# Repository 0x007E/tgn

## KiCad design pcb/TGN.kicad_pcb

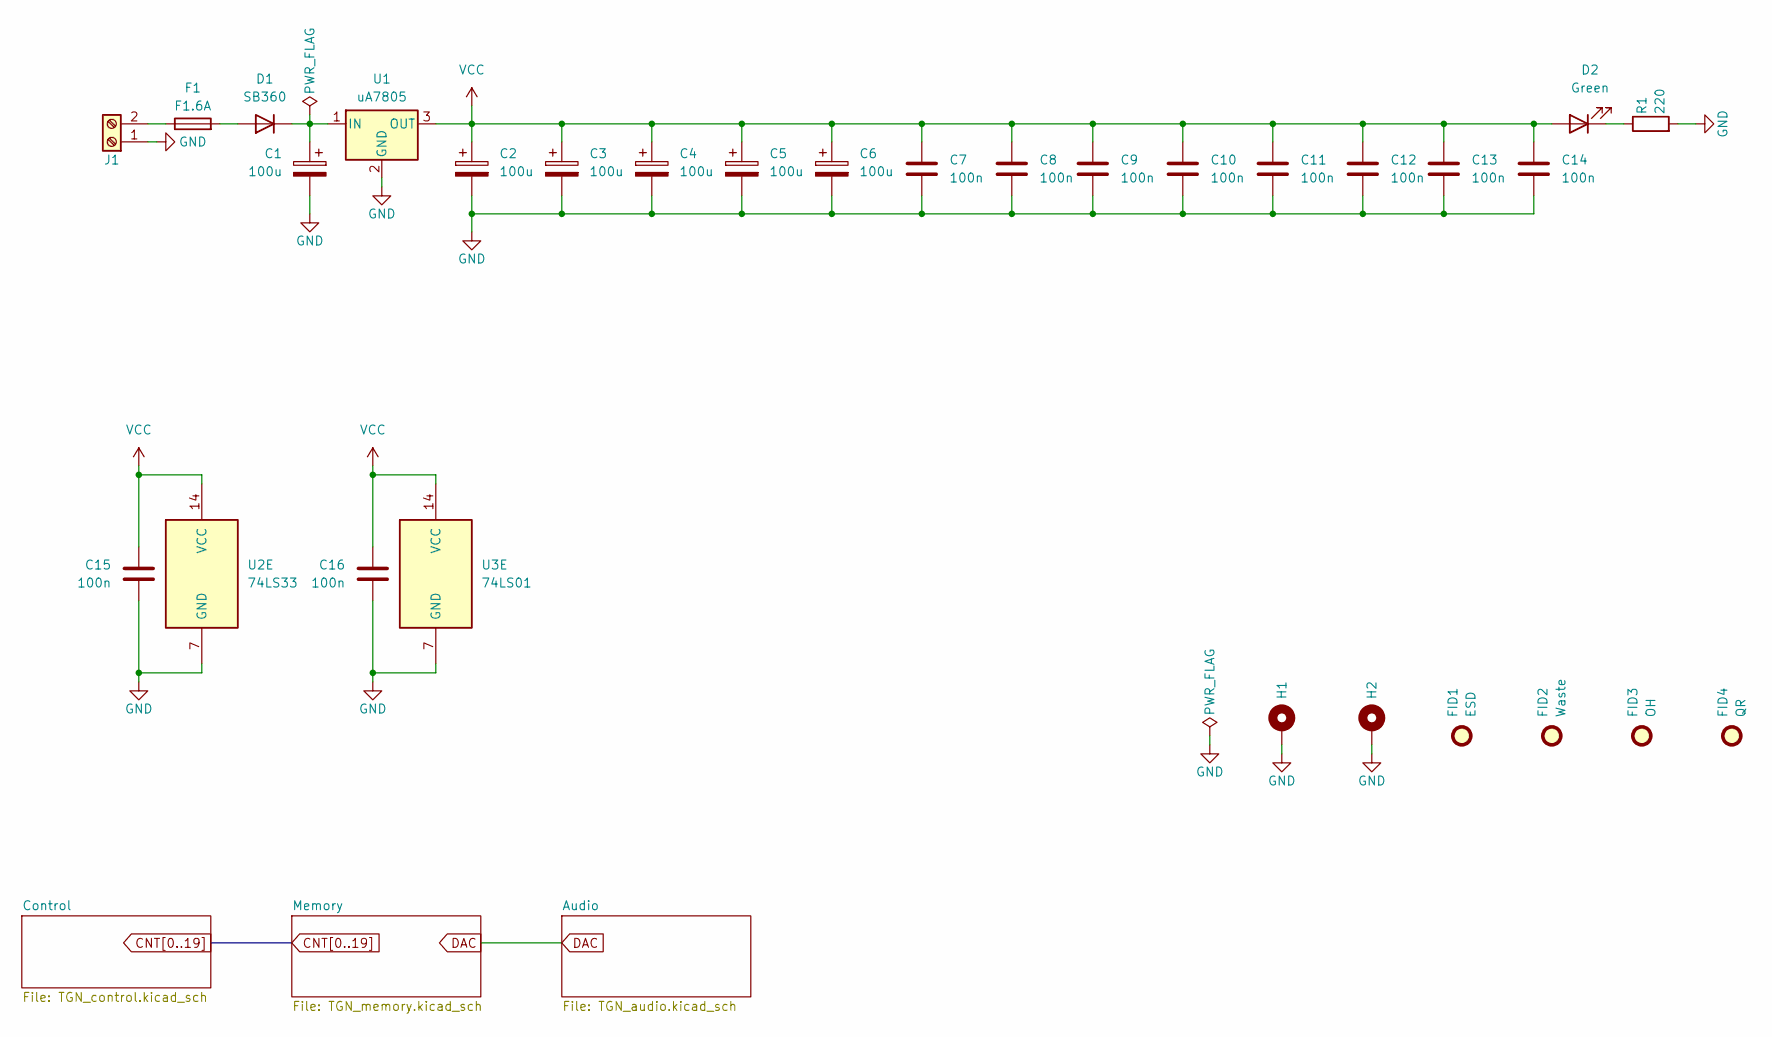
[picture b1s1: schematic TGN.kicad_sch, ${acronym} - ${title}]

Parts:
C1, C2, C3, C4, C5, C6: 100u; CP_Radial_D8.0mm_P3.50mm
C7, C8, C9, C10, C11, C12, C13, C14, C15, C16: 100n; C_Disc_D5.0mm_W2.5mm_P2.50mm
D1: SB360; D_DO-201_P15.24mm_Horizontal
D2: Green; LED_D5.0mm
F1: F1.6A; Fuse_20mm_HTL
FID1: ESD; ESD-Logo_6.6x6mm_SilkScreen
FID2: Waste; WEEE-Logo_4.2x6mm_SilkScreen
FID3: OH; OSHW-Logo_5.7x6mm_SilkScreen
FID4: QR; QR_0x007e_small
H1, H2: MountingHole_Pad; MountingHole_3.2mm_M3_Pad
J1: Screw_Terminal_01x02; TerminalBlock_Phoenix_MKDS-1,5-2-5.08_1x02_P5.08mm_Horizont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
R1: 220; R_Axial_DIN0207_L6.3mm_D2.5mm_P10.16mm_Horizontal
U1: uA7805; TO-220-3_Vertical
U2: 74LS33; DIP-14_W7.62mm_Socket_LongPads
U3: 74LS01; DIP-14_W7.62mm_Socket_LongPads

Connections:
GND: C1.2, C2.2, C3.2, C4.2, C5.2, C6.2, C7.2, C8.2, C9.2, C10.2, C11.2, C12.2, C13.2, C14.2, C15.2, C16.2, H1.1, H2.1, J1.1, R1.2, U1.2 (GND), U2.7 (GND), U3.7 (GND); also elsewhere on the board
unnamed: D1.2 (A), F1.2
unnamed: C1.1, D1.1 (K), U1.1 (IN)
unnamed: D2.1 (K), R1.1
unnamed: F1.1, J1.2
VCC: C2.1, C3.1, C4.1, C5.1, C6.1, C7.1, C8.1, C9.1, C10.1, C11.1, C12.1, C13.1, C14.1, C15.1, C16.1, D2.2 (A), U1.3 (OUT), U2.14 (VCC), U3.14 (VCC); also elsewhere on the board

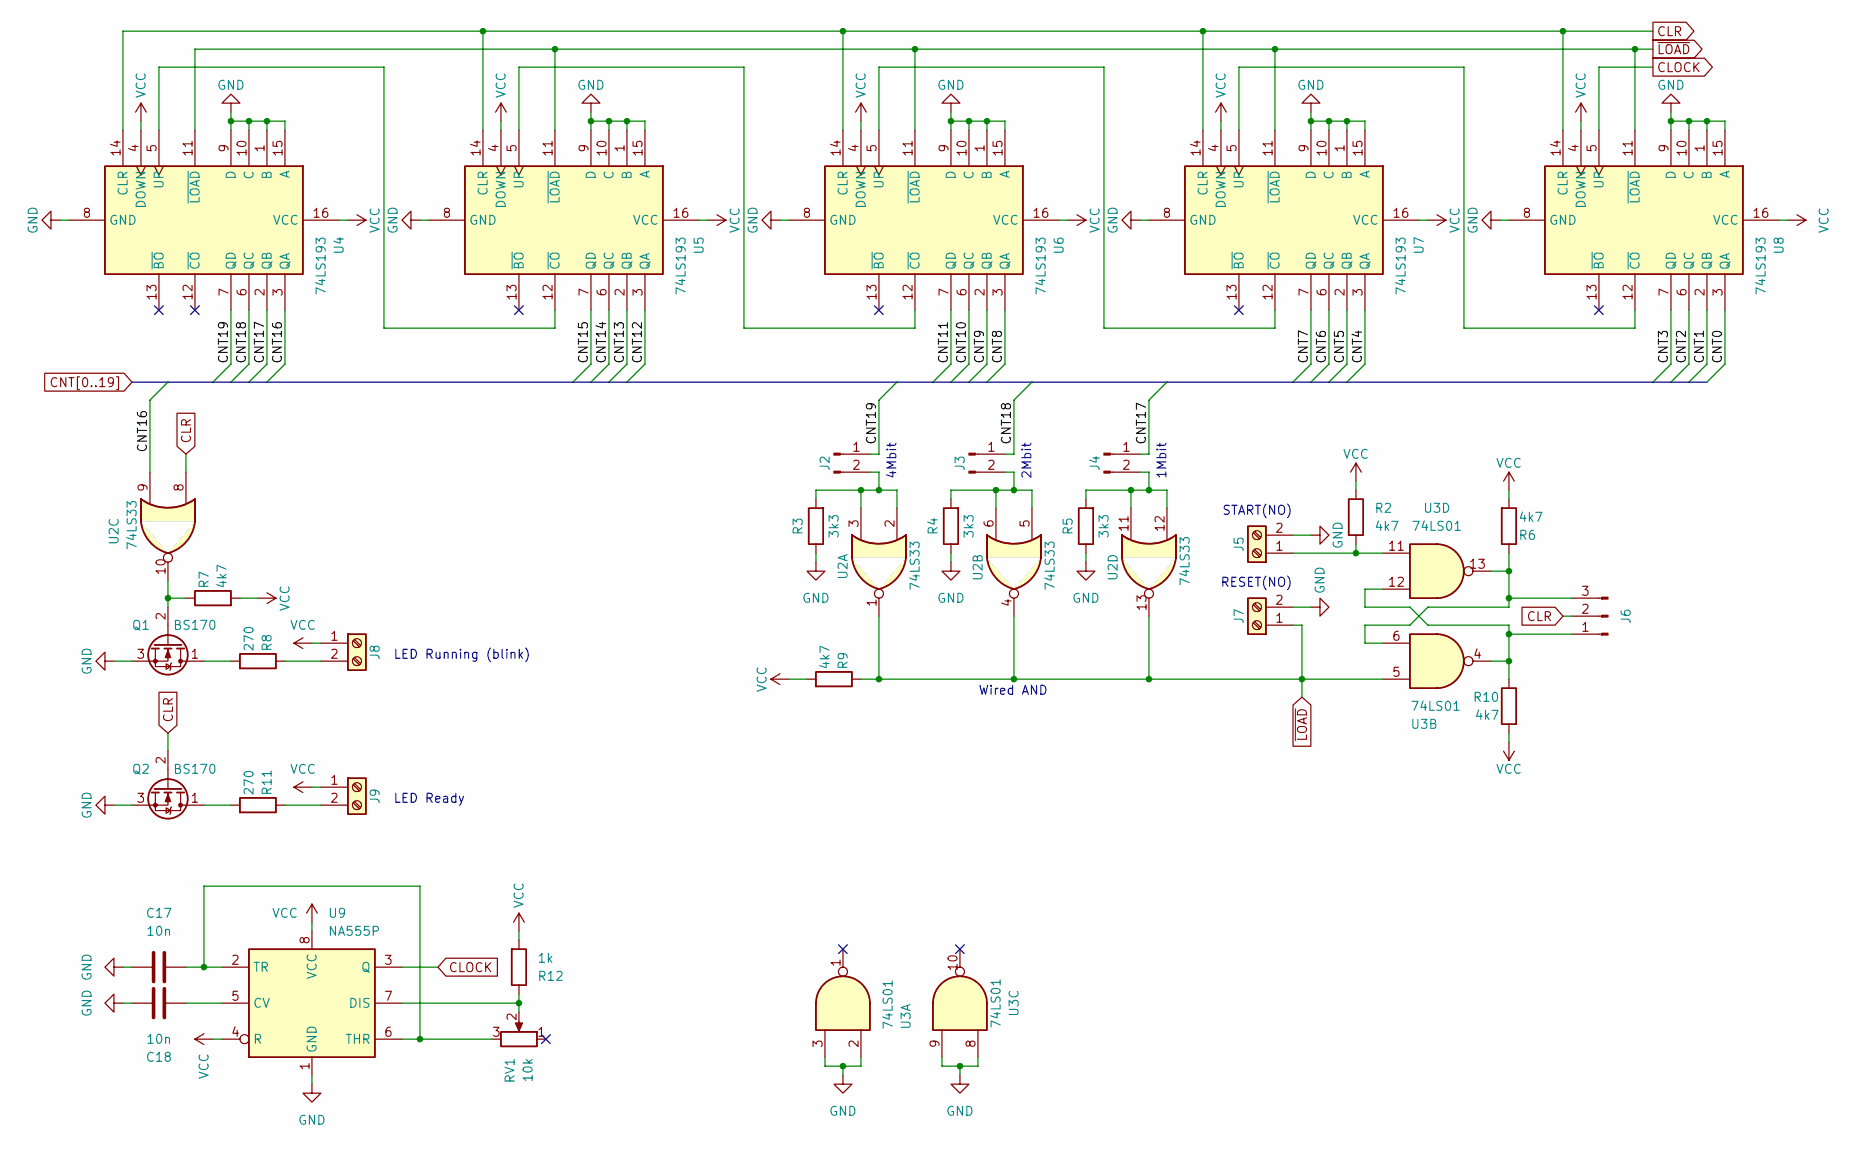
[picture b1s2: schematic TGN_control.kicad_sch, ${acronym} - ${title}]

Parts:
C17, C18: 10n; C_Disc_D5.0mm_W2.5mm_P2.50mm
J2, J3, J4: Conn_01x02_Pin; PinHeader_1x02_P2.54mm_Vertical
J5, J7, J8, J9: Screw_Terminal_01x02; TerminalBlock_Phoenix_MKDS-1,5-2-5.08_1x02_P5.08mm_Horizont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
J6: Conn_01x03_Pin; PinHeader_1x03_P2.54mm_Vertical
Q1, Q2: BS170; TO-92_Wide
R2, R6, R7, R9, R10: 4k7; R_Axial_DIN0207_L6.3mm_D2.5mm_P10.16mm_Horizontal
R3, R4, R5: 3k3; R_Axial_DIN0207_L6.3mm_D2.5mm_P10.16mm_Horizontal
R8, R11: 270; R_Axial_DIN0207_L6.3mm_D2.5mm_P10.16mm_Horizontal
R12: 1k; R_Axial_DIN0207_L6.3mm_D2.5mm_P10.16mm_Horizontal
RV1: 10k; Potentiometer_Bourns_3296W_Vertical
U2: 74LS33; DIP-14_W7.62mm_Socket_LongPads
U3: 74LS01; DIP-14_W7.62mm_Socket_LongPads
U4, U5, U6, U7, U8: 74LS193; DIP-16_W7.62mm_Socket_LongPads
U9: NA555P; DIP-8_W7.62mm_Socket_LongPads

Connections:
CLOCK: U8.5 (UP), U9.3 (Q)
CLR: J6.2, Q2.2 (G), U2.8, U4.14 (CLR), U5.14 (CLR), U6.14 (CLR), U7.14 (CLR), U8.14 (CLR)
CNT0: U8.3 (QA); also elsewhere on the board
CNT1: U8.2 (QB); also elsewhere on the board
CNT2: U8.6 (QC); also elsewhere on the board
CNT3: U8.7 (QD); also elsewhere on the board
CNT4: U7.3 (QA); also elsewhere on the board
CNT5: U7.2 (QB); also elsewhere on the board
CNT6: U7.6 (QC); also elsewhere on the board
CNT7: U7.7 (QD); also elsewhere on the board
CNT8: U6.3 (QA); also elsewhere on the board
CNT9: U6.2 (QB); also elsewhere on the board
CNT10: U6.6 (QC); also elsewhere on the board
CNT11: U6.7 (QD); also elsewhere on the board
CNT12: U5.3 (QA); also elsewhere on the board
CNT13: U5.2 (QB); also elsewhere on the board
CNT14: U5.6 (QC); also elsewhere on the board
CNT15: U5.7 (QD); also elsewhere on the board
CNT16: U2.9, U4.3 (QA); also elsewhere on the board
CNT17: J4.1, U4.2 (QB); also elsewhere on the board
CNT18: J3.1, U4.6 (QC); also elsewhere on the board
CNT19: J2.1, U4.7 (QD)
GND: C17.1, C18.1, J5.2, J7.2, Q1.3 (S), Q2.3 (S), R3.1, R4.1, R5.1, U3.2, U3.3, U3.8, U3.9, U4.1 (B), U4.8 (GND), U4.9 (D), U4.10 (C), U4.15 (A), U5.1 (B), U5.8 (GND), U5.9 (D), U5.10 (C), U5.15 (A), U6.1 (B), U6.8 (GND), U6.9 (D), U6.10 (C), U6.15 (A), U7.1 (B), U7.8 (GND), U7.9 (D), U7.10 (C), U7.15 (A), U8.1 (B), U8.8 (GND), U8.9 (D), U8.10 (C), U8.15 (A), U9.1 (GND); also elsewhere on the board
unnamed: J2.2, R3.2, U2.2, U2.3
unnamed: J3.2, R4.2, U2.5, U2.6
unnamed: J4.2, R5.2, U2.11, U2.12
unnamed: J5.1, R2.2, U3.11
unnamed: J6.1, R10.1, U3.4, U3.12
unnamed: J6.3, R6.1, U3.6, U3.13
unnamed: J8.2, R8.1
unnamed: J9.2, R11.1
unnamed: Q1.1 (D), R8.2
unnamed: Q1.2 (G), R7.1, U2.10
unnamed: Q2.1 (D), R11.2
unnamed: U4.5 (UP), U5.12 (~CO)
unnamed: U5.5 (UP), U6.12 (~CO)
unnamed: U6.5 (UP), U7.12 (~CO)
unnamed: U7.5 (UP), U8.12 (~CO)
unnamed: C18.2, U9.5 (CV)
unnamed: R12.1, RV1.2, U9.7 (DIS)
unnamed: C17.2, RV1.3, U9.2 (TR), U9.6 (THR)
VCC: J8.1, J9.1, R2.1, R6.2, R7.2, R9.2, R10.2, R12.2, U4.4 (DOWN), U4.16 (VCC), U5.4 (DOWN), U5.16 (VCC), U6.4 (DOWN), U6.16 (VCC), U7.4 (DOWN), U7.16 (VCC), U8.4 (DOWN), U8.16 (VCC), U9.4 (R), U9.8 (VCC); also elsewhere on the board
~LOAD: J7.1, R9.1, U2.1, U2.4, U2.13, U3.5, U4.11 (~LOAD), U5.11 (~LOAD), U6.11 (~LOAD), U7.11 (~LOAD), U8.11 (~LOAD)

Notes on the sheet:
Wired AND
2Mbit
4Mbit
LED Ready
1Mbit
LED Running (blink)
RESET(NO)
START(NO)

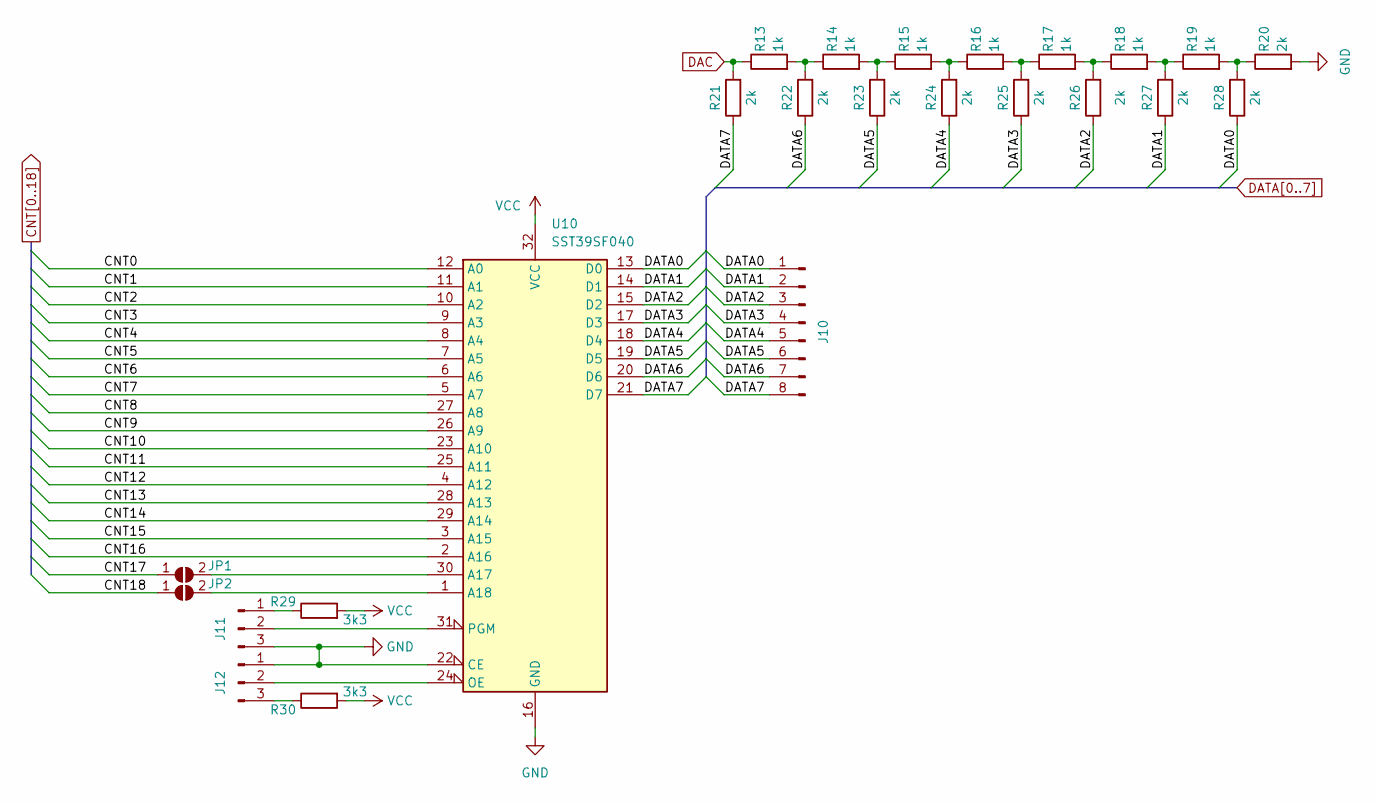
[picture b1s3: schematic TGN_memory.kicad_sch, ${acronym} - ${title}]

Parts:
J10: Conn_01x08_Pin; PinSocket_1x08_P2.54mm_Vertical
J11, J12: Conn_01x03_Pin; PinHeader_1x03_P2.54mm_Vertical
JP1, JP2: SolderJumper_2_Open; SolderJumper-2_P1.3mm_Open_RoundedPad1.0x1.5mm
R13, R14, R15, R16, R17, R18, R19: 1k; R_Axial_DIN0207_L6.3mm_D2.5mm_P10.16mm_Horizontal
R20, R21, R22, R23, R24, R25, R26, R27, R28: 2k; R_Axial_DIN0207_L6.3mm_D2.5mm_P10.16mm_Horizontal
R29, R30: 3k3; R_Axial_DIN0207_L6.3mm_D2.5mm_P10.16mm_Horizontal
U10: SST39SF040; DIP-32_W15.24mm_LongPads

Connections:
CNT0: U10.12 (A0); also elsewhere on the board
CNT1: U10.11 (A1); also elsewhere on the board
CNT2: U10.10 (A2); also elsewhere on the board
CNT3: U10.9 (A3); also elsewhere on the board
CNT4: U10.8 (A4); also elsewhere on the board
CNT5: U10.7 (A5); also elsewhere on the board
CNT6: U10.6 (A6); also elsewhere on the board
CNT7: U10.5 (A7); also elsewhere on the board
CNT8: U10.27 (A8); also elsewhere on the board
CNT9: U10.26 (A9); also elsewhere on the board
CNT10: U10.23 (A10); also elsewhere on the board
CNT11: U10.25 (A11); also elsewhere on the board
CNT12: U10.4 (A12); also elsewhere on the board
CNT13: U10.28 (A13); also elsewhere on the board
CNT14: U10.29 (A14); also elsewhere on the board
CNT15: U10.3 (A15); also elsewhere on the board
CNT16: U10.2 (A16); also elsewhere on the board
CNT17: JP1.1 (A); also elsewhere on the board
CNT18: JP2.1 (A); also elsewhere on the board
DAC: R13.1, R21.2; also elsewhere on the board
DATA0: J10.1, R28.1, U10.13 (D0)
DATA1: J10.2, R27.1, U10.14 (D1)
DATA2: J10.3, R26.1, U10.15 (D2)
DATA3: J10.4, R25.1, U10.17 (D3)
DATA4: J10.5, R24.1, U10.18 (D4)
DATA5: J10.6, R23.1, U10.19 (D5)
DATA6: J10.7, R22.1, U10.20 (D6)
DATA7: J10.8, R21.1, U10.21 (D7)
GND: J11.3, J12.1, R20.2, U10.16 (GND), U10.22 (CE); also elsewhere on the board
unnamed: J11.1, R29.1
unnamed: J11.2, U10.31 (PGM)
unnamed: J12.2, U10.24 (OE)
unnamed: J12.3, R30.1
unnamed: JP1.2 (B), U10.30 (A17)
unnamed: JP2.2 (B), U10.1 (A18)
unnamed: R13.2, R14.1, R22.2
unnamed: R14.2, R15.1, R23.2
unnamed: R15.2, R16.1, R24.2
unnamed: R16.2, R17.1, R25.2
unnamed: R17.2, R18.1, R26.2
unnamed: R18.2, R19.1, R27.2
unnamed: R19.2, R20.1, R28.2
VCC: R29.2, R30.2, U10.32 (VCC); also elsewhere on the board

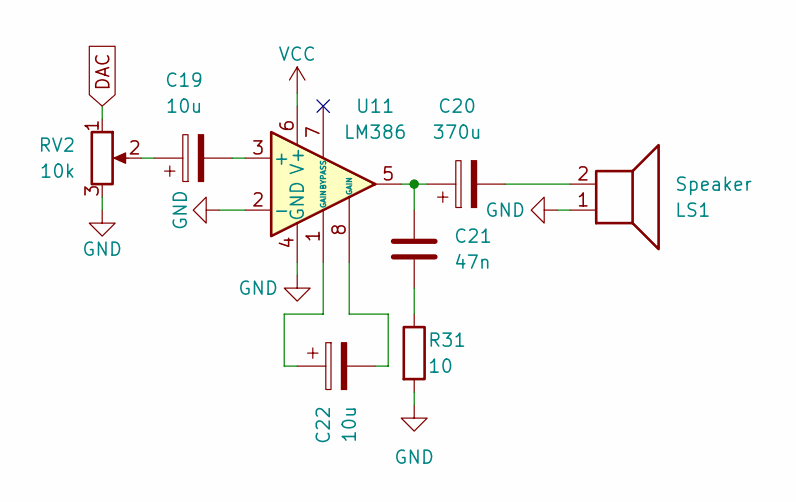
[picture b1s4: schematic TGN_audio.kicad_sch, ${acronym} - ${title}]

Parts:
C19, C22: 10u; CP_Radial_D8.0mm_P3.50mm
C20: 370u; CP_Radial_D8.0mm_P3.50mm
C21: 47n; C_Disc_D5.0mm_W2.5mm_P2.50mm
LS1: Speaker; TerminalBlock_Phoenix_MKDS-1,5-2-5.08_1x02_P5.08mm_Horizont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
R31: 10; R_Axial_DIN0207_L6.3mm_D2.5mm_P10.16mm_Horizontal
RV2: 10k; Potentiometer_Piher_PT-10-V10_Vertical
U11: LM386; DIP-8_W7.62mm_Socket_LongPads

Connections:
DAC: RV2.1; also elsewhere on the board
GND: LS1.1, R31.2, RV2.3, U11.2 (-), U11.4 (GND); also elsewhere on the board
unnamed: C19.1, RV2.2
unnamed: C20.1, C21.1, U11.5
unnamed: C20.2, LS1.2
unnamed: C21.2, R31.1
unnamed: C22.1, U11.1 (GAIN)
unnamed: C22.2, U11.8 (GAIN)
unnamed: C19.2, U11.3 (+)
VCC: U11.6 (V+); also elsewhere on the board

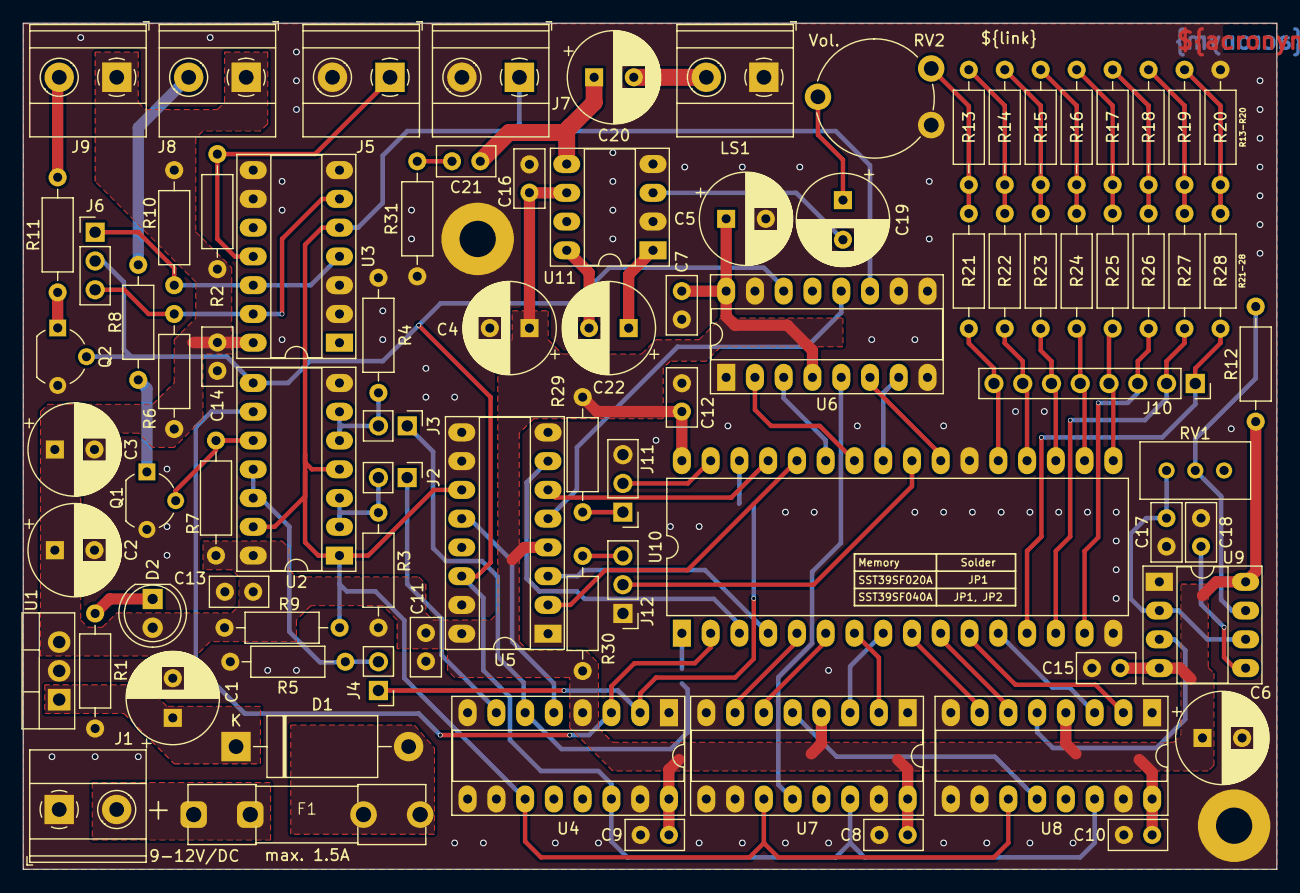
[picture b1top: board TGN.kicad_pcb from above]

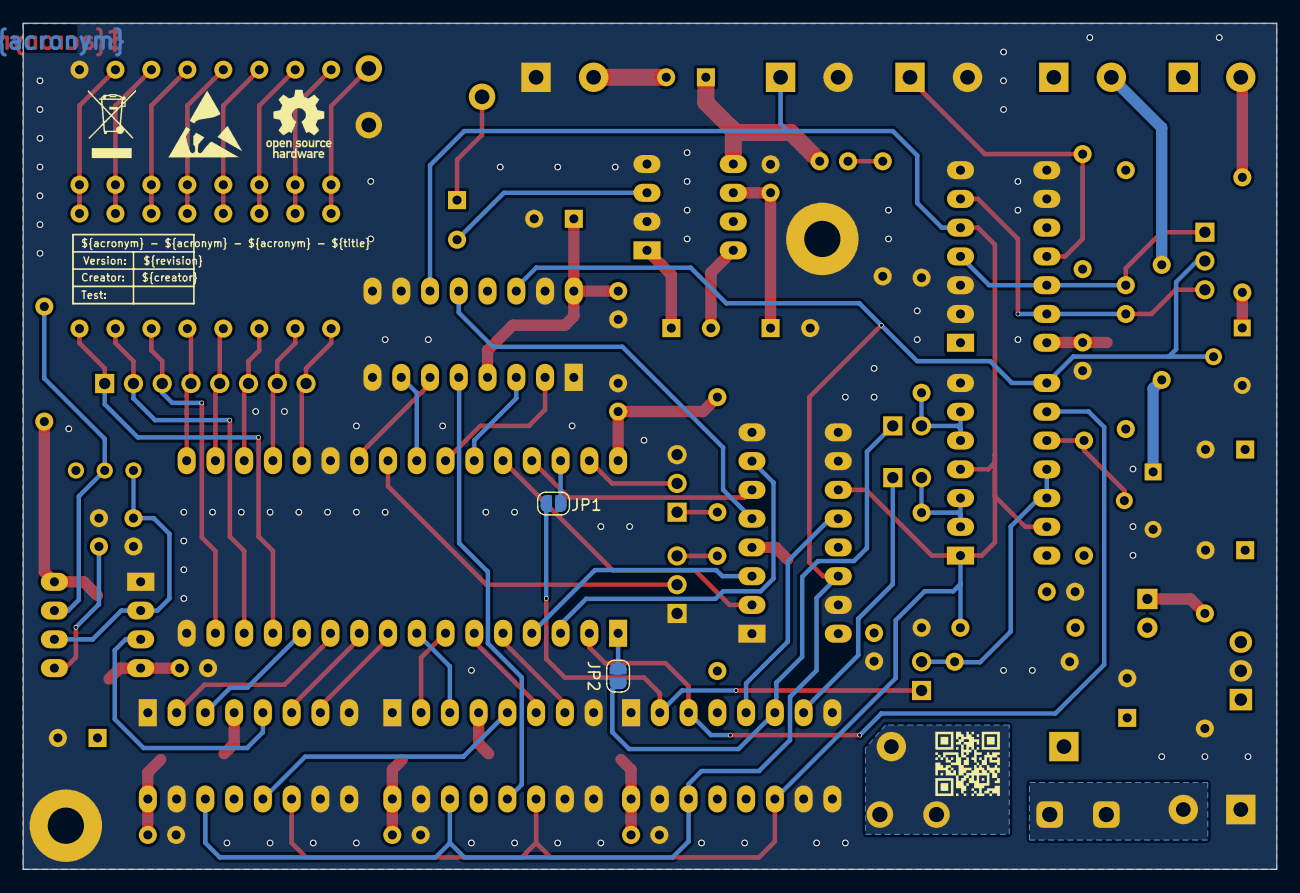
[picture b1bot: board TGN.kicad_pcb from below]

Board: 2 copper layers, 110.7 x 74.7 mm, 92 parts (6 on the bottom side), 76 nets.

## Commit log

2026-02-20 Add pcb layout
2026-02-20 Adapt ladder resistor values
2026-03-04 Rename LICENSE
2026-03-04 Add build pipeline
2026-04-12 Add dimensioning
2026-04-12 Add mechanical parts
2026-04-13 Add heat sink
2026-04-13 Add mounting screws and spacers
2026-04-15 Expand pg diameter

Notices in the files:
parts and their libraries:
license: CC BY-NC-SA 4.0
